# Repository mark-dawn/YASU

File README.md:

# YASU

## What's this?
__Yet Another Saturn__ to __USB__ is a small pet project with 3 aims:
1. Connect a couple of Saturn controllers to my PC for retrogaming
2. Learn how the USB protocol works
3. Learn how to make a PCB and other hardware shenanigans

While I do not expect it to blow anyone's mind, I believe that the code and board turned out quite good
and are usable both in practice and for learning purposes.

## Hardware support
For now only the standard Saturn controller is supported, and has been tested with Japanese `HSS-0101` controllers.

However the code is structured so it should be easy to add support for other Saturn peripherals;
for sure, support for the _3D Controller_ is planned since I own one of those.

Support for the Saturn Mouse might be harder since the board should reconfigure itself as a pointer HID device at enumeration time.

## Note about contacts
The connection between board and the Saturn plug is handled quite rudimentary at the moment.
Flat naked metal pads on tabs that fit inside the cavity of the plug are present,
but cannot make direct contact with the pads in the plug.

For now the "intended" way is to solder extension metal pads to make contact,
but it is quite hard to solder those manually and the connection can act shaky.

In the future I plan to swap those out for flat pogo pins, or if no suitable part exists, use a proper 3D printed receptacle.

## Credits
This project would have not been as easy as it was without various resources from the Internets.
* Objective development for the excellent [v-usb library](https://github.com/obdev/v-usb)
* [Raphaël Assénat](http://www.raphnet.net/index_en), that has a similar [project](http://www.raphnet.net/electronique/saturn_usb/index_en.php) with excellent documentation
* https://gamesx.com/controldata/saturn.htm for a starting point on how to read the standard controller
* Any kind soul that has written small tutorials for ~~messy sintax~~ makefiles

## TODO
* Fix contact between board and Saturn Plug
* Add support for 3D pad
* Extend credits list, expecially for HID configuration examples
* Look into how licenses work since v-usb is under the GPL-2, and go around and slap it in the files that necessitate it
* Add better documentation to `Saturn.c` to clarify which bits are getting extracted without having to look at the header file

## License
All the repository is licensed under the GPL-3. See `LICENSE` for more info.

    Copyright (C) 2022  Marica Albanesi

    This program is free software: you can redistribute it and/or modify
    it under the terms of the GNU General Public License as published by
    the Free Software Foundation, either version 3 of the License, or
    (at your option) any later version.

    This program is distributed in the hope that it will be useful,
    but WITHOUT ANY WARRANTY; without even the implied warranty of
    MERCHANTABILITY or FITNESS FOR A PARTICULAR PURPOSE.  See the
    GNU General Public License for more details.

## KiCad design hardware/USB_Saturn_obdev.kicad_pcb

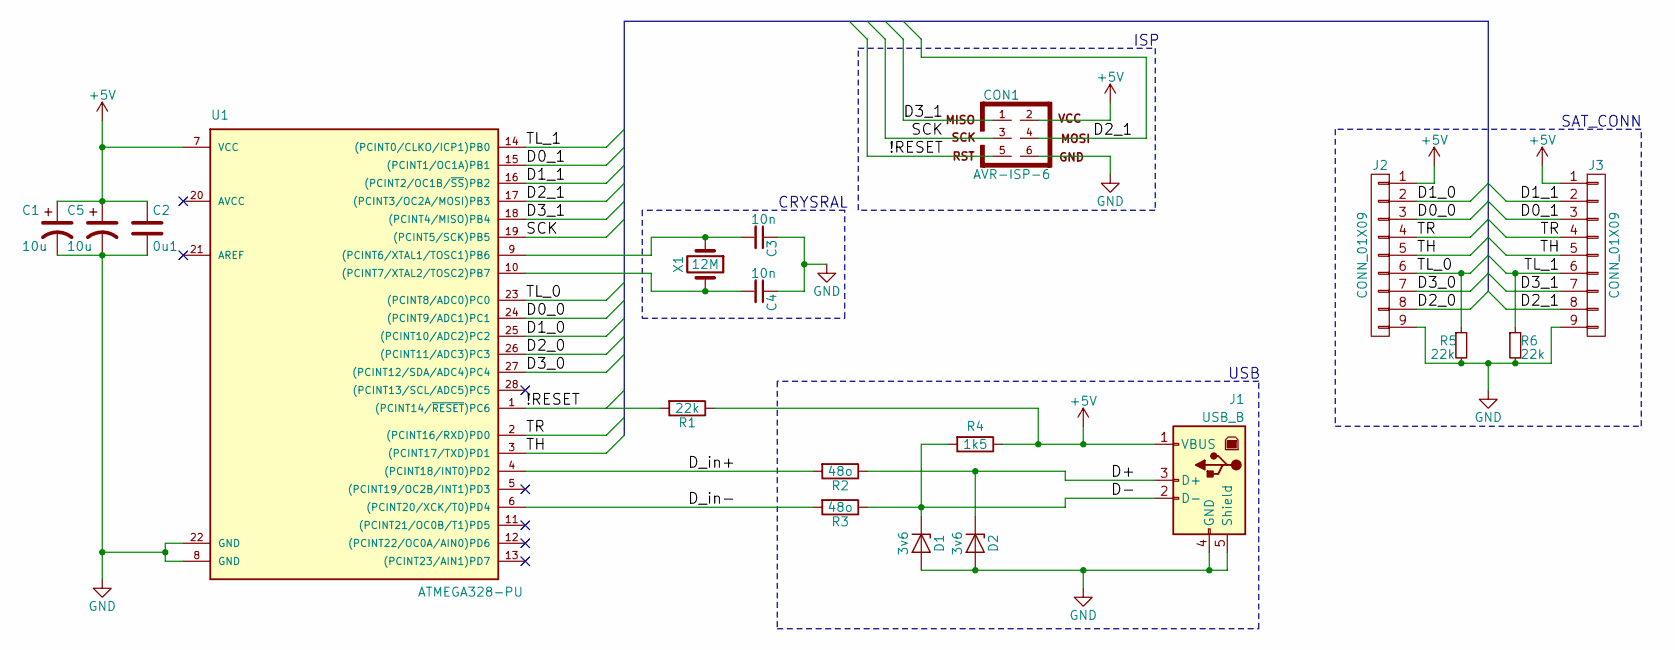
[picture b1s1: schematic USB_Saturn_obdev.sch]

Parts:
C1, C5: 10u; CP_Radial_D4.0mm_P2.00mm
C2: 0u1; C_Disc_D3.4mm_W2.1mm_P2.50mm
C3, C4: 10n; C_Disc_D3.4mm_W2.1mm_P2.50mm
CON1: AVR-ISP-6; PinHeader_2x03_P2.54mm_Vertical
D1, D2: 3v6; D_T-1_P5.08mm_Horizontal
J1: USB_B; USB_B_OST_USB-B1HSxx_Horizontal
J2, J3: CONN_01X09; Saturn_f_standalone
R1, R5, R6: 22k; R_Axial_DIN0207_L6.3mm_D2.5mm_P10.16mm_Horizontal
R2, R3: 48o; R_Axial_DIN0207_L6.3mm_D2.5mm_P10.16mm_Horizontal
R4: 1k5; R_Axial_DIN0207_L6.3mm_D2.5mm_P10.16mm_Horizontal
U1: ATMEGA328-PU; DIP-28_W7.62mm
X1: 12M; Crystal_HC49-4H_Vertical

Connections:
+5V: C1.1, C2.1, C5.1, CON1.2, J1.1 (VBUS), J2.1, J3.1, R1.1, R4.1, U1.7 (VCC)
/!RESET: CON1.5, R1.2, U1.1 ((PCINT14/~RESET~)PC6)
/D0_0: J2.3, U1.24 ((PCINT9/ADC1)PC1)
/D0_1: J3.3, U1.15 ((PCINT1/OC1A)PB1)
/D1_0: J2.2, U1.25 ((PCINT10/ADC2)PC2)
/D1_1: J3.2, U1.16 ((PCINT2/OC1B/~SS~)PB2)
/D2_0: J2.8, U1.26 ((PCINT11/ADC3)PC3)
/D2_1: CON1.4, J3.8, U1.17 ((PCINT3/OC2A/MOSI)PB3)
/D3_0: J2.7, U1.27 ((PCINT12/SDA/ADC4)PC4)
/D3_1: CON1.1, J3.7, U1.18 ((PCINT4/MISO)PB4)
/D+: D2.1 (K), J1.3 (D+), R2.1
/D-: D1.1 (K), J1.2 (D-), R3.1, R4.2
/D_in+: R2.2, U1.4 ((PCINT18/INT0)PD2)
/D_in-: R3.2, U1.6 ((PCINT20/XCK/T0)PD4)
/SCK: CON1.3, U1.19 ((PCINT5/SCK)PB5)
/TH: J2.5, J3.5, U1.3 ((PCINT17/TXD)PD1)
/TL_0: J2.6, R5.1, U1.23 ((PCINT8/ADC0)PC0)
/TL_1: J3.6, R6.1, U1.14 ((PCINT0/CLKO/ICP1)PB0)
/TR: J2.4, J3.4, U1.2 ((PCINT16/RXD)PD0)
GND: C1.2, C2.2, C3.1, C4.1, C5.2, CON1.6, D1.2 (A), D2.2 (A), J1.4 (GND), J1.5 (Shield), J2.9, J3.9, R5.2, R6.2, U1.8 (GND), U1.22 (GND)
unnamed: C3.2, U1.9 ((PCINT6/XTAL1/TOSC1)PB6), X1.1
unnamed: C4.2, U1.10 ((PCINT7/XTAL2/TOSC2)PB7), X1.2

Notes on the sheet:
USB
ISP
CRYSRAL
SAT_CONN

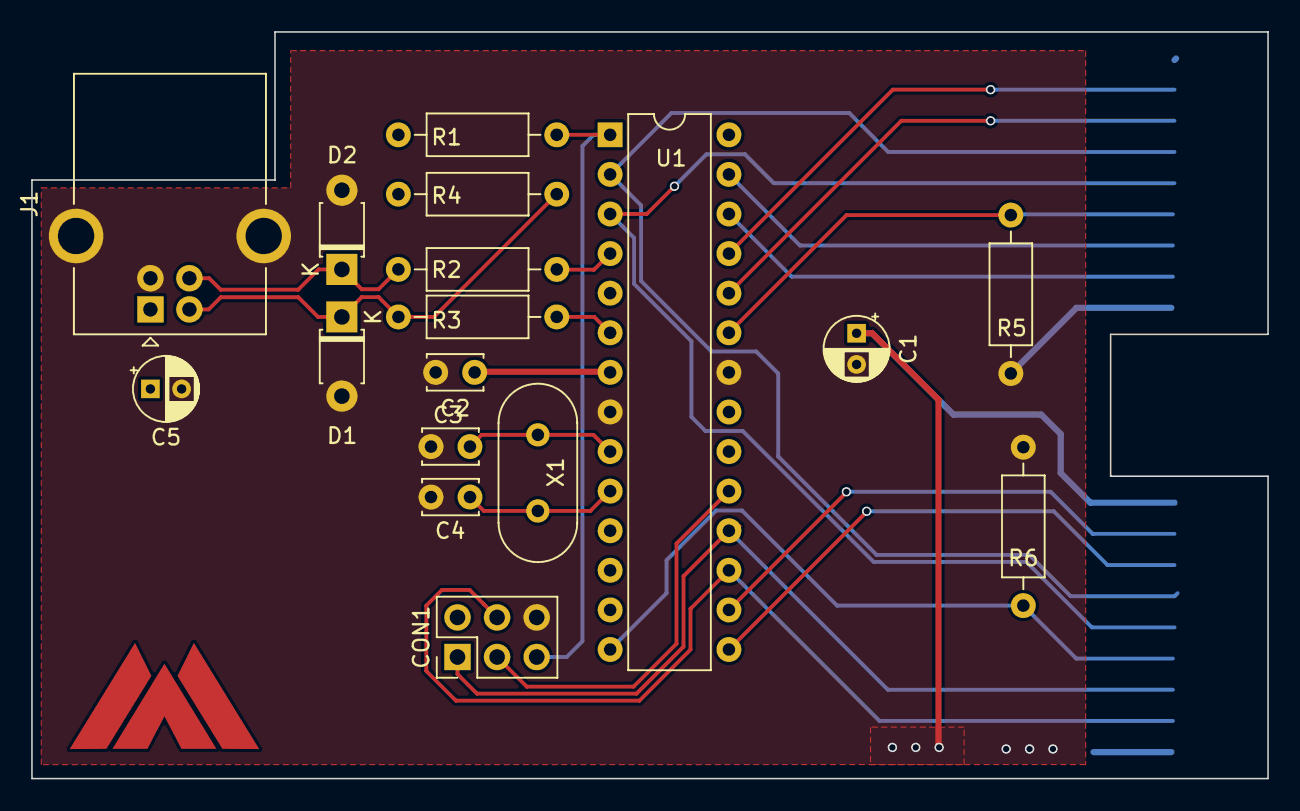
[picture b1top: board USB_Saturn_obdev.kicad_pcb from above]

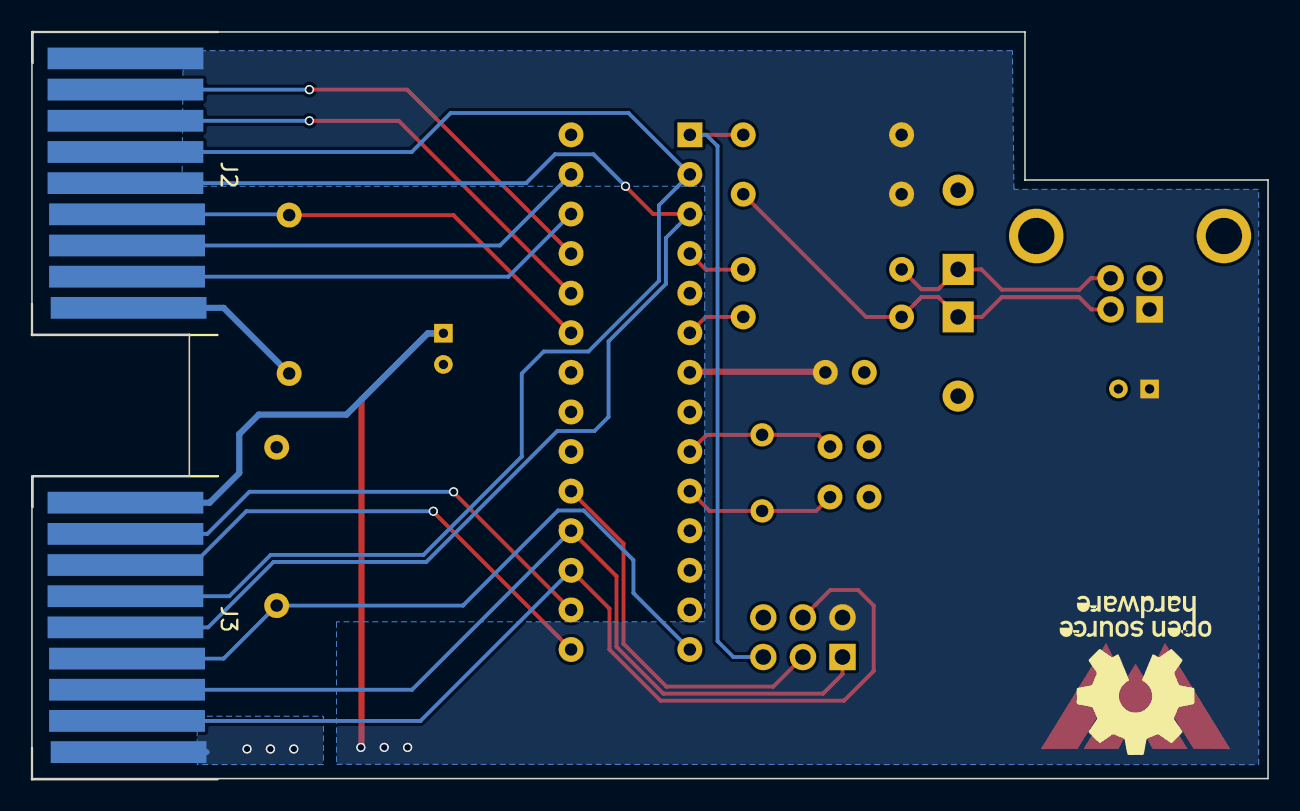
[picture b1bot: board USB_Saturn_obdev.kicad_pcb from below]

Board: 2 copper layers, 79.3 x 47.9 mm, 21 parts (3 on the bottom side), 22 nets.

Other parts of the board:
logo_MA2: G***; logo_MA2
svg2mod: G***; osh_silk

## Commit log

2018-06-26 Initial commit
    Most of the project is in a working state
2018-06-27 Added LICENSE and README
2018-06-27 Remove bak files from hardware/
    try to get v-usb to show up as a submodule
2018-07-14 Added backup library
    Changed logos
2019-04-18 Kicad format changes
2022-01-17 add Dockerfile
2022-01-17 add docker compose
2022-01-17 add dockerignore
2026-03-30 Reduced timing between updates
